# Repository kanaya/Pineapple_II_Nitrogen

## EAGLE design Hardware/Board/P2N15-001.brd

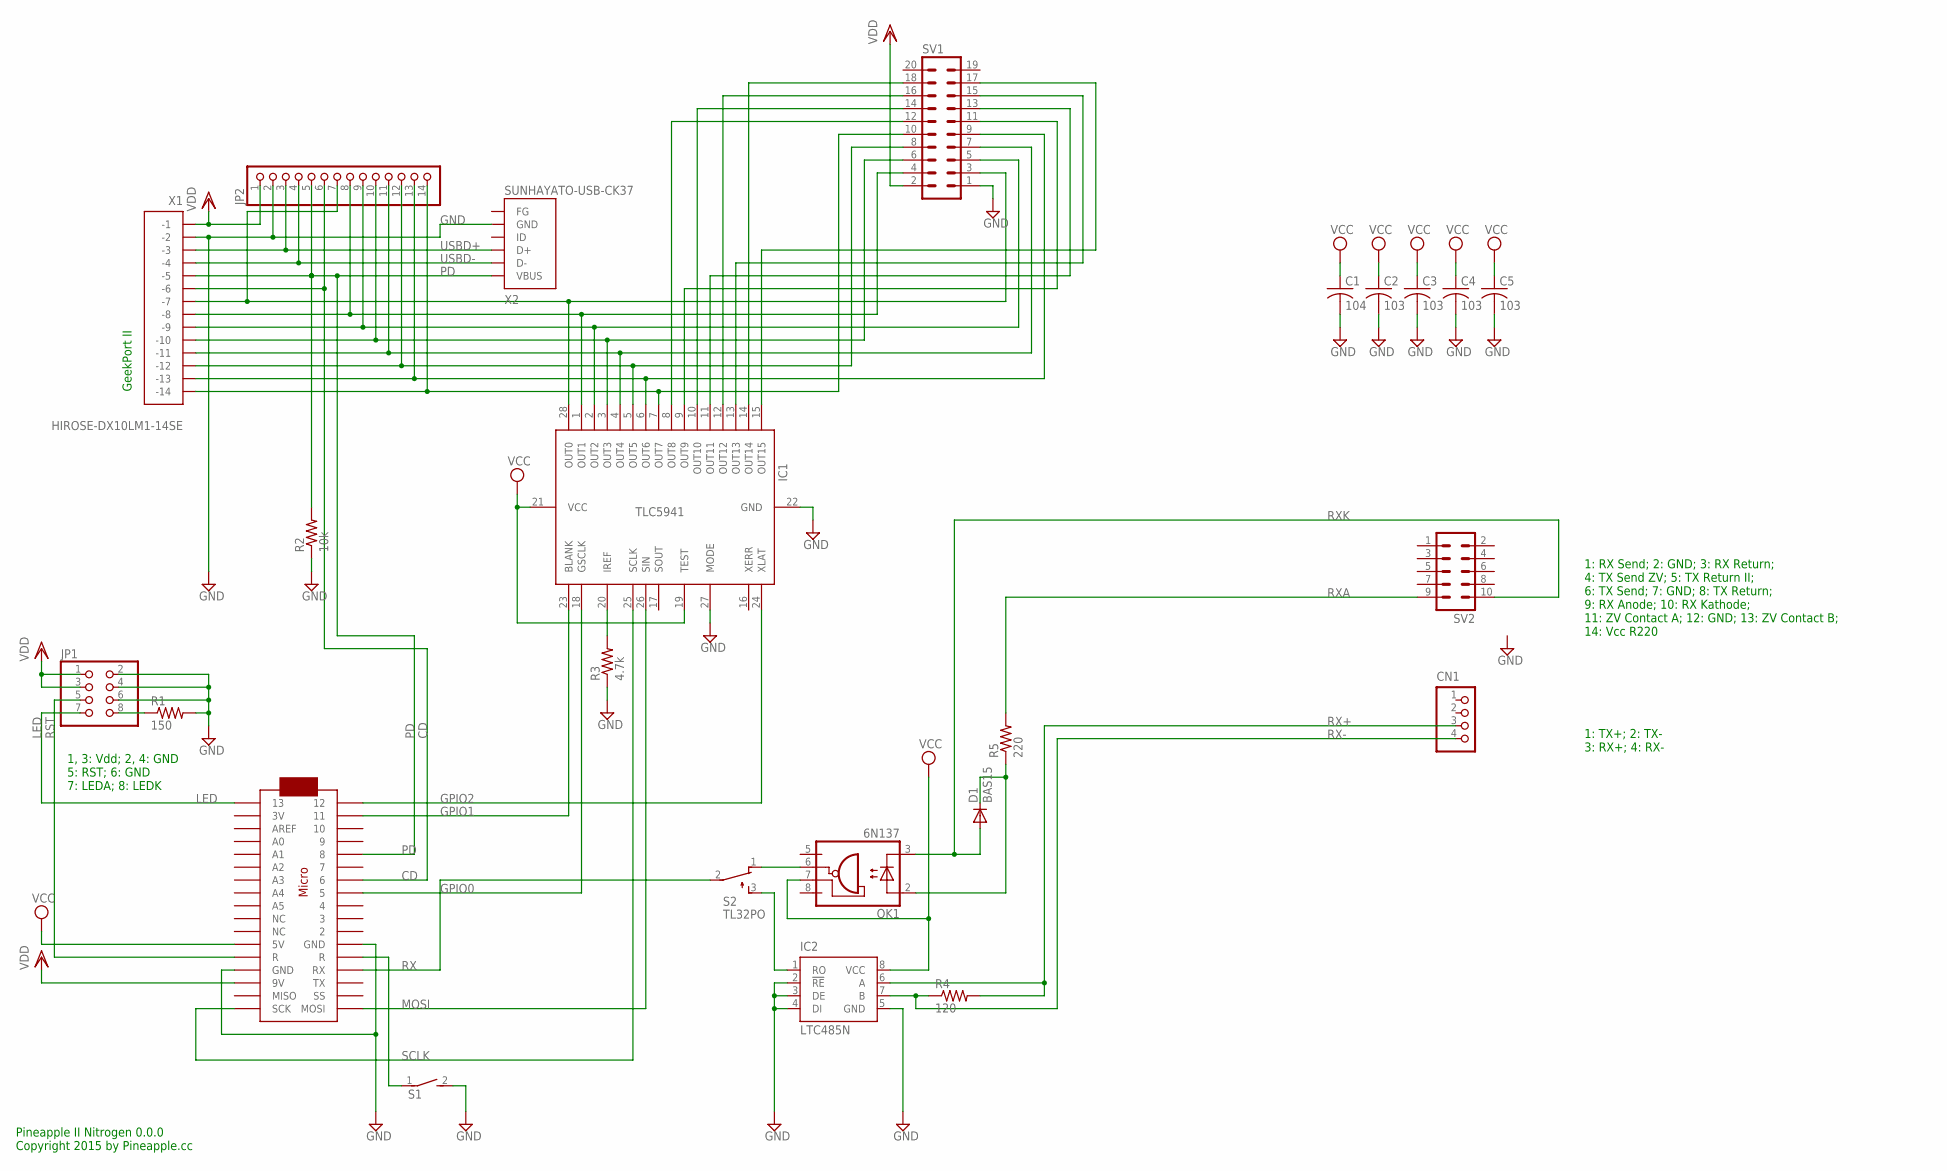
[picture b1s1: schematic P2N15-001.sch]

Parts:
C1: 104; C025-025X050
C2, C3, C4, C5: 103; C025-025X050
CN1: S4B-PH-K-S
D1: BAS15; DO34-7
IC1: TLC5941NT; DIL28-3
IC2: LTC485N; DIL08
JP1: PINHD-2X4; 2X04
JP2: PINHD-1X14-CB; 1X14-CB
MC1: ARDUINOMICRO
OK1: 6N137; DIL08
R1: 150; 0204/5
R2: 10k; 0204/5
R3: 4.7k; 0204/5
R4: 120; 0204/5
R5: 220; 0204/5
S1: DS01E; DS-01
S2: TL32PO; TL3XPO
SV1: ML20L
SV2: ML10L
X1: HIROSE-DX10LM1-14SE
X2: SUNHAYATO-USB-CK37

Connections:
CD: JP2.6, MC1.P$7 (6), X1.P$6 (-6)
GND: C1.2, C2.2, C3.2, C4.2, C5.2, IC1.22 (GND), IC1.27 (MODE), IC2.2 (!RE), IC2.3 (DE), IC2.4 (DI), IC2.5 (GND), JP1.2, JP1.4, JP1.6, JP2.2, MC1.P$12 (GND), MC1.P$21 (GND), R1.2, R2.1, R3.1, S1.2, SV1.1, X1.P$2 (-2), X2.P$5 (GND)
GPIO0: IC1.18 (GSCLK), MC1.P$8 (5)
GPIO1: IC1.23 (BLANK), MC1.P$2 (11)
GPIO2: IC1.24 (XLAT), MC1.P$1 (12)
LED: JP1.7, MC1.P$34 (13)
MIDIRX: OK1.6 (VO), S2.1 (O)
MOSI: IC1.26 (SIN), MC1.P$17 (MOSI)
unnamed: MC1.P$22 (R), S1.1
unnamed: IC2.1 (RO), S2.3 (S)
unnamed: IC1.28 (OUT0), JP2.7, SV1.3, X1.P$7 (-7)
unnamed: IC1.20 (IREF), R3.2
unnamed: IC1.7 (OUT7), JP2.14, SV1.10, X1.P$14 (-14)
unnamed: IC1.8 (OUT8), SV1.12
unnamed: IC1.1 (OUT1), JP2.8, SV1.4, X1.P$8 (-8)
unnamed: IC1.9 (OUT9), SV1.11
unnamed: IC1.2 (OUT2), JP2.9, SV1.5, X1.P$9 (-9)
unnamed: IC1.3 (OUT3), JP2.10, SV1.6, X1.P$10 (-10)
unnamed: IC1.4 (OUT4), JP2.11, SV1.7, X1.P$11 (-11)
unnamed: IC1.10 (OUT10), SV1.14
unnamed: IC1.11 (OUT11), SV1.13
unnamed: IC1.12 (OUT12), SV1.16
unnamed: D1.C, OK1.2 (A), R5.1
unnamed: IC1.13 (OUT13), SV1.15
unnamed: IC1.14 (OUT14), SV1.18
unnamed: IC1.15 (OUT15), SV1.17
unnamed: IC1.5 (OUT5), JP2.12, SV1.8, X1.P$12 (-12)
unnamed: IC1.6 (OUT6), JP2.13, SV1.9, X1.P$13 (-13)
unnamed: JP1.8, R1.1
PD: JP2.5, MC1.P$5 (8), R2.2, X1.P$5 (-5), X2.P$1 (VBUS)
RST: JP1.5, MC1.P$13 (R)
RX: MC1.P$14 (RX), S2.2
RX+: CN1.3, IC2.6 (A), R4.2
RX-: CN1.4, IC2.7 (B), R4.1
RXA: R5.2, SV2.9
RXK: D1.A, OK1.3 (C), SV2.10
SCLK: IC1.25 (SCLK), MC1.P$18 (SCK)
USBD+: JP2.3, X1.P$3 (-3), X2.P$3 (D+)
USBD-: JP2.4, X1.P$4 (-4), X2.P$2 (D-)
VCC: C1.1, C2.1, C3.1, C4.1, C5.1, IC1.19 (TEST), IC1.21 (VCC), IC2.8 (VCC), MC1.P$23 (5V), OK1.7 (VE)
VDD: JP1.1, JP1.3, JP2.1, MC1.P$20 (9V), SV1.2, X1.P$1 (-1)

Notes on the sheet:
Pineapple II Nitrogen 0.0.0 Copyright 2015 by Pineapple.cc
1, 3: Vdd; 2, 4: GND 5: RST; 6: GND 7: LEDA; 8: LEDK
GeekPort II
1: TX+; 2: TX- 3: RX+; 4: RX-
1: RX Send; 2: GND; 3: RX Return; 4: TX Send ZV; 5: TX Return II; 6: TX Send; 7: GND; 8: TX Return; 9: RX Anode; 10: RX Kathode; 11: ZV Contact A; 12: GND; 13: ZV Contact B; 14: Vcc R220

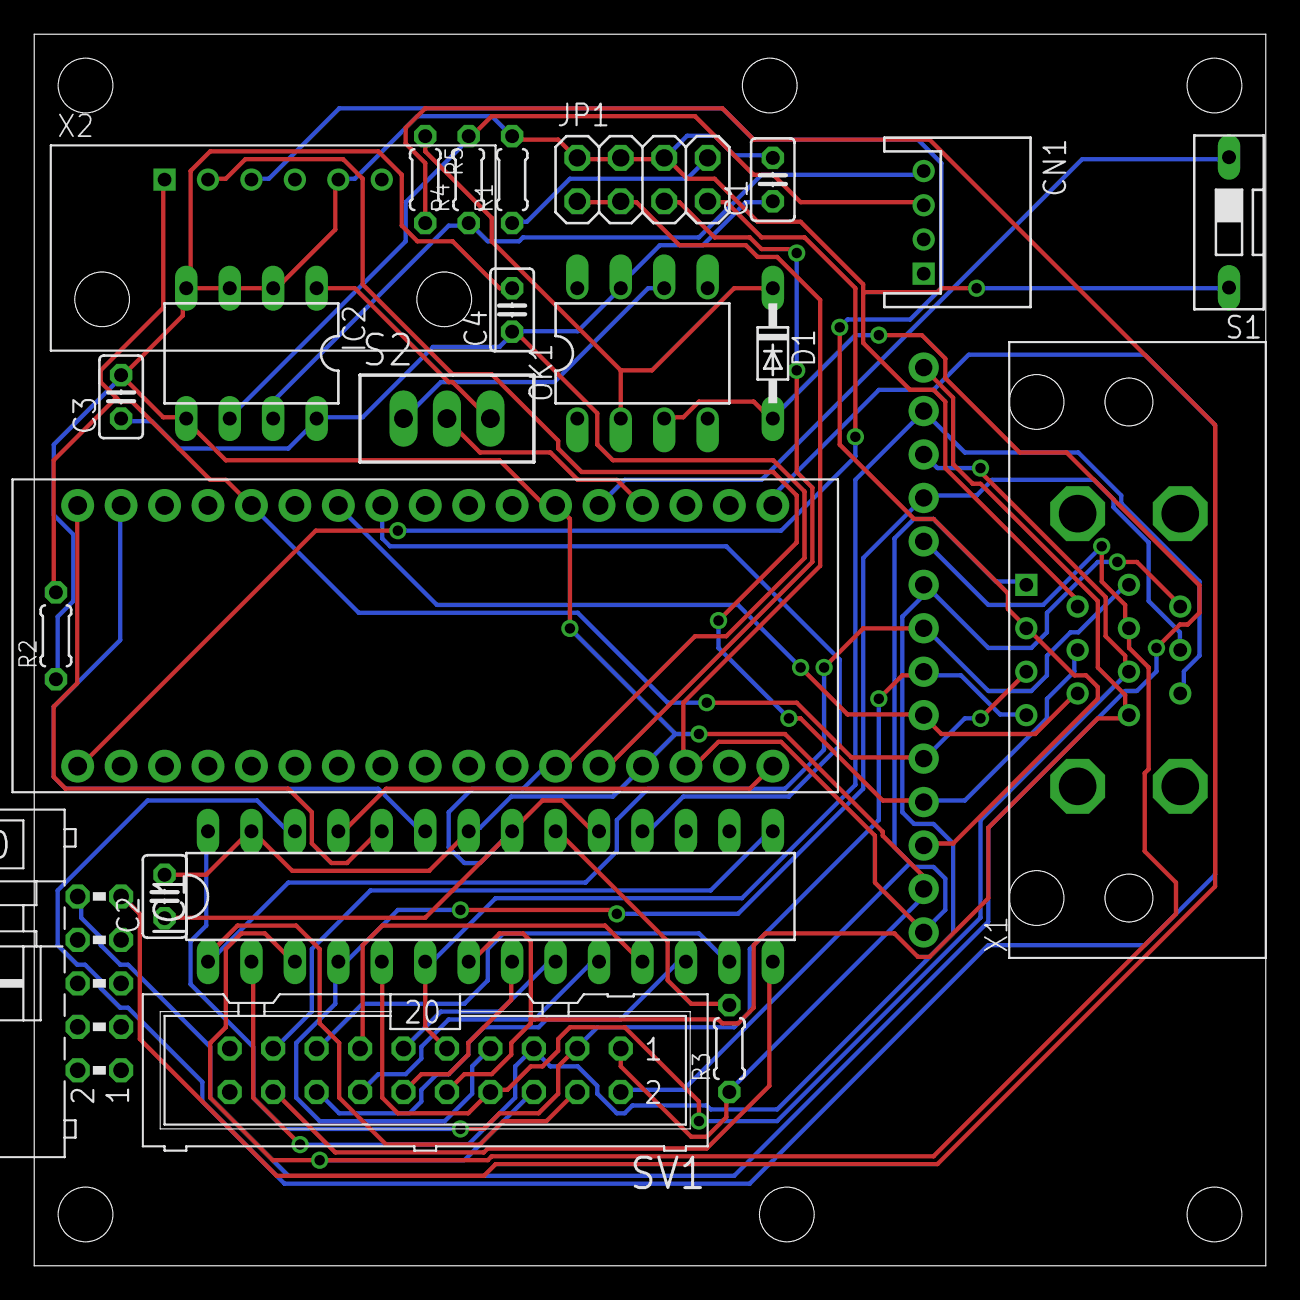
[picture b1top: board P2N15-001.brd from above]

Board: 2 copper layers, 72.0 x 72.0 mm, 23 parts (0 on the bottom side), 41 nets.

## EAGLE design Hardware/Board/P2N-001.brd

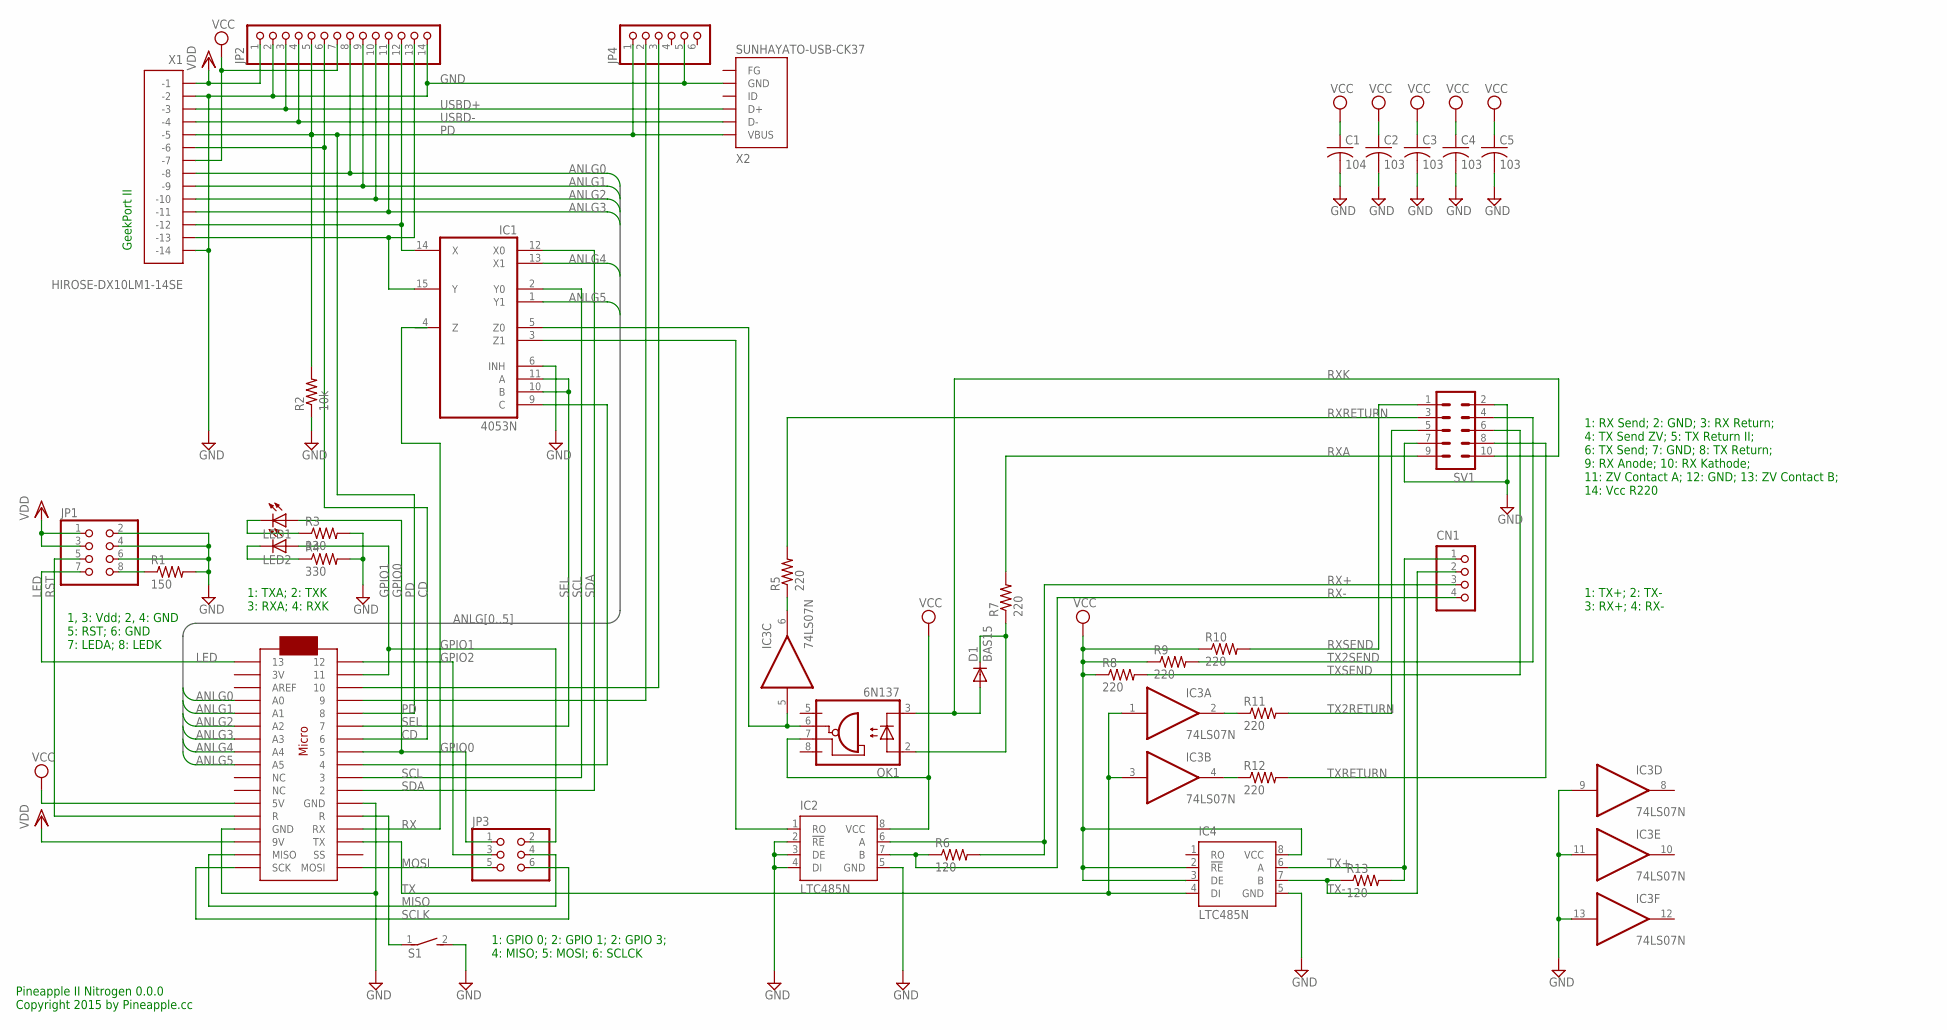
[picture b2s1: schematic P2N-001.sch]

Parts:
C1: 104; C025-025X050
C2, C3, C4, C5: 103; C025-025X050
CN1: S4B-PH-K-S
D1: BAS15; DO34-7
IC1: 4053N; DIL16
IC2, IC4: LTC485N; DIL08
IC3: 74LS07N; DIL14
JP1: PINHD-2X4; 2X04
JP2: PINHD-1X14-CB; 1X14-CB
JP3: PINHD-2X3; 2X03
JP4: PINHD-1X6; 1X06
LED1, LED2: LED3MM
MC1: ARDUINOMICRO
OK1: 6N137; DIL08
R1: 150; 0204/5
R2: 10k; 0204/5
R3, R4: 330; 0204/5
R5, R7, R8, R9, R10, R11, R12: 220; 0204/5
R6, R13: 120; 0204/5
S1: DS01E; DS-01
SV1: ML10L
X1: HIROSE-DX10LM1-14SE
X2: SUNHAYATO-USB-CK37

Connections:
ANLG0: JP2.8, MC1.P$31 (A0), X1.P$8 (-8)
ANLG1: JP2.9, MC1.P$30 (A1), X1.P$9 (-9)
ANLG2: JP2.10, MC1.P$29 (A2), X1.P$10 (-10)
ANLG3: JP2.11, MC1.P$28 (A3), X1.P$11 (-11)
ANLG4: IC1.13 (X1), MC1.P$27 (A4)
ANLG5: IC1.1 (Y1), MC1.P$26 (A5)
CD: JP2.6, MC1.P$7 (6), X1.P$6 (-6)
GND: C1.2, C2.2, C3.2, C4.2, C5.2, IC1.6 (INH), IC1.8 (GND), IC2.2 (!RE), IC2.3 (DE), IC2.4 (DI), IC2.5 (GND), IC3.7 (GND), IC3.9 (I), IC3.11 (I), IC3.13 (I), IC4.5 (GND), JP1.2, JP1.4, JP1.6, JP2.2, JP2.14, JP4.5, MC1.P$12 (GND), MC1.P$21 (GND), R1.2, R2.1, R3.2, R4.2, S1.2, SV1.2, SV1.7, X1.P$2 (-2), X1.P$14 (-14), X2.P$5 (GND)
GPIO0: JP3.1, LED1.A, MC1.P$8 (5)
GPIO1: JP3.2, LED2.A, MC1.P$2 (11)
GPIO2: JP3.3, MC1.P$1 (12)
LED: JP1.7, MC1.P$34 (13)
MIDIRX: IC1.5 (Z0), IC3.5 (I), OK1.6 (VO)
MISO: JP3.4, MC1.P$19 (MISO)
MOSI: JP3.5, MC1.P$17 (MOSI)
unnamed: MC1.P$22 (R), S1.1
unnamed: IC3.2 (O), R11.1
unnamed: IC3.6 (O), R5.1
unnamed: IC3.4 (O), R12.1
unnamed: JP4.2, MC1.P$4 (9)
unnamed: JP4.3, MC1.P$3 (10)
unnamed: IC1.9 (C), MC1.P$9 (4)
unnamed: D1.C, OK1.2 (A), R7.1
unnamed: LED1.K (C), R3.1
unnamed: LED2.K (C), R4.1
unnamed: IC1.14 (X), JP2.12, X1.P$12 (-12)
unnamed: IC1.15 (Y), JP2.13, X1.P$13 (-13)
unnamed: JP1.8, R1.1
PD: JP2.5, JP4.1, MC1.P$5 (8), R2.2, X1.P$5 (-5), X2.P$1 (VBUS)
RST: JP1.5, MC1.P$13 (R)
RX: MC1.P$14 (RX)
RX+: CN1.3, IC2.6 (A), R6.2
RX-: CN1.4, IC2.7 (B), R6.1
RXA: R7.2, SV1.9
RXK: D1.A, OK1.3 (C), SV1.10
RXRETURN: R5.2, SV1.3
RXSEND: R10.2, SV1.1
SCL: IC1.2 (Y0), MC1.P$10 (3)
SCLK: JP3.6, MC1.P$18 (SCK)
SDA: IC1.12 (X0), MC1.P$11 (2)
SEL: IC1.10 (B), IC1.11 (A), MC1.P$6 (7)
TX: IC3.1 (I), IC3.3 (I), IC4.4 (DI), MC1.P$15 (TX)
TX2RETURN: R11.2, SV1.5
TX2SEND: R9.2, SV1.4
TX+: CN1.1, IC4.6 (A), R13.2
TX-: CN1.2, IC4.7 (B), R13.1
TXRETURN: R12.2, SV1.8
TXSEND: R8.2, SV1.6
USBD+: JP2.3, X1.P$3 (-3), X2.P$3 (D+)
USBD-: JP2.4, X1.P$4 (-4), X2.P$2 (D-)
VCC: C1.1, C2.1, C3.1, C4.1, C5.1, IC1.16 (VCC), IC2.8 (VCC), IC3.14 (VCC), IC4.2 (!RE), IC4.3 (DE), IC4.8 (VCC), JP2.7, MC1.P$23 (5V), OK1.7 (VE), R8.1, R9.1, R10.1, X1.P$7 (-7)
VDD: JP1.1, JP1.3, JP2.1, MC1.P$20 (9V), X1.P$1 (-1)
VEE: IC1.7 (VEE)
XMIDIRX: IC1.3 (Z1), IC2.1 (RO)

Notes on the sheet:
Pineapple II Nitrogen 0.0.0 Copyright 2015 by Pineapple.cc
1, 3: Vdd; 2, 4: GND 5: RST; 6: GND 7: LEDA; 8: LEDK
GeekPort II
1: TXA; 2: TXK 3: RXA; 4: RXK
1: TX+; 2: TX- 3: RX+; 4: RX-
1: GPIO 0; 2: GPIO 1; 2: GPIO 3; 4: MISO; 5: MOSI; 6: SCLCK
1: RX Send; 2: GND; 3: RX Return; 4: TX Send ZV; 5: TX Return II; 6: TX Send; 7: GND; 8: TX Return; 9: RX Anode; 10: RX Kathode; 11: ZV Contact A; 12: GND; 13: ZV Contact B; 14: Vcc R220

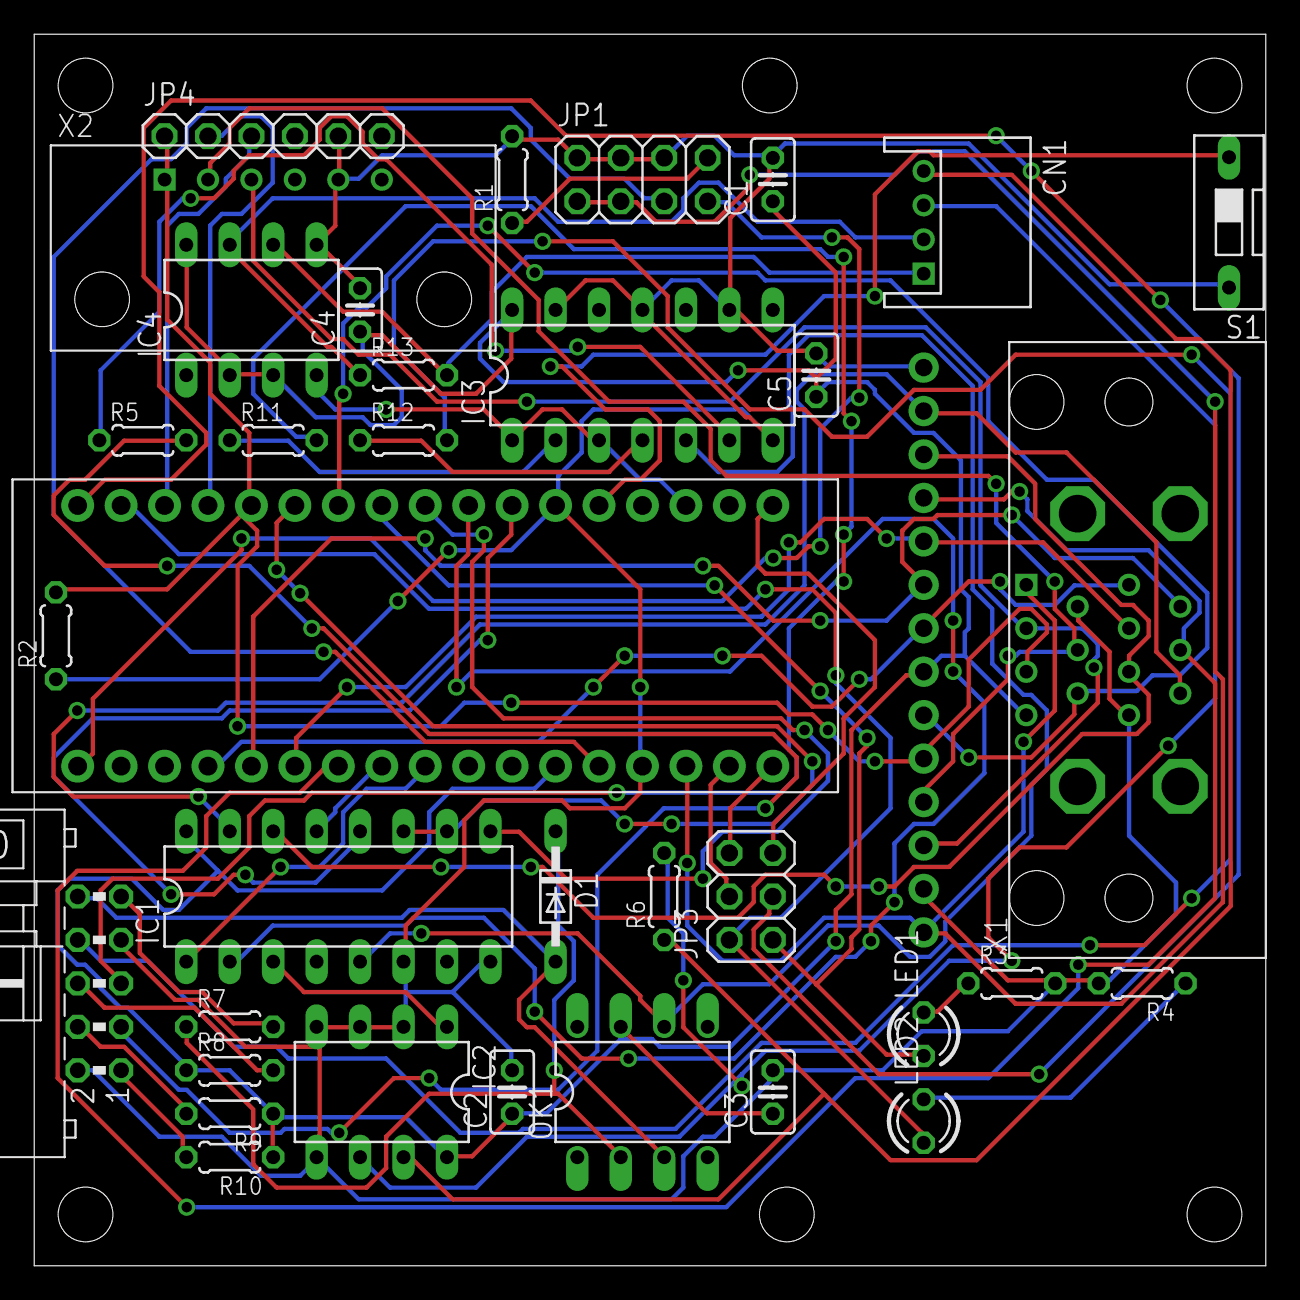
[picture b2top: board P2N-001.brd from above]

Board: 2 copper layers, 72.0 x 72.0 mm, 36 parts (0 on the bottom side), 52 nets.

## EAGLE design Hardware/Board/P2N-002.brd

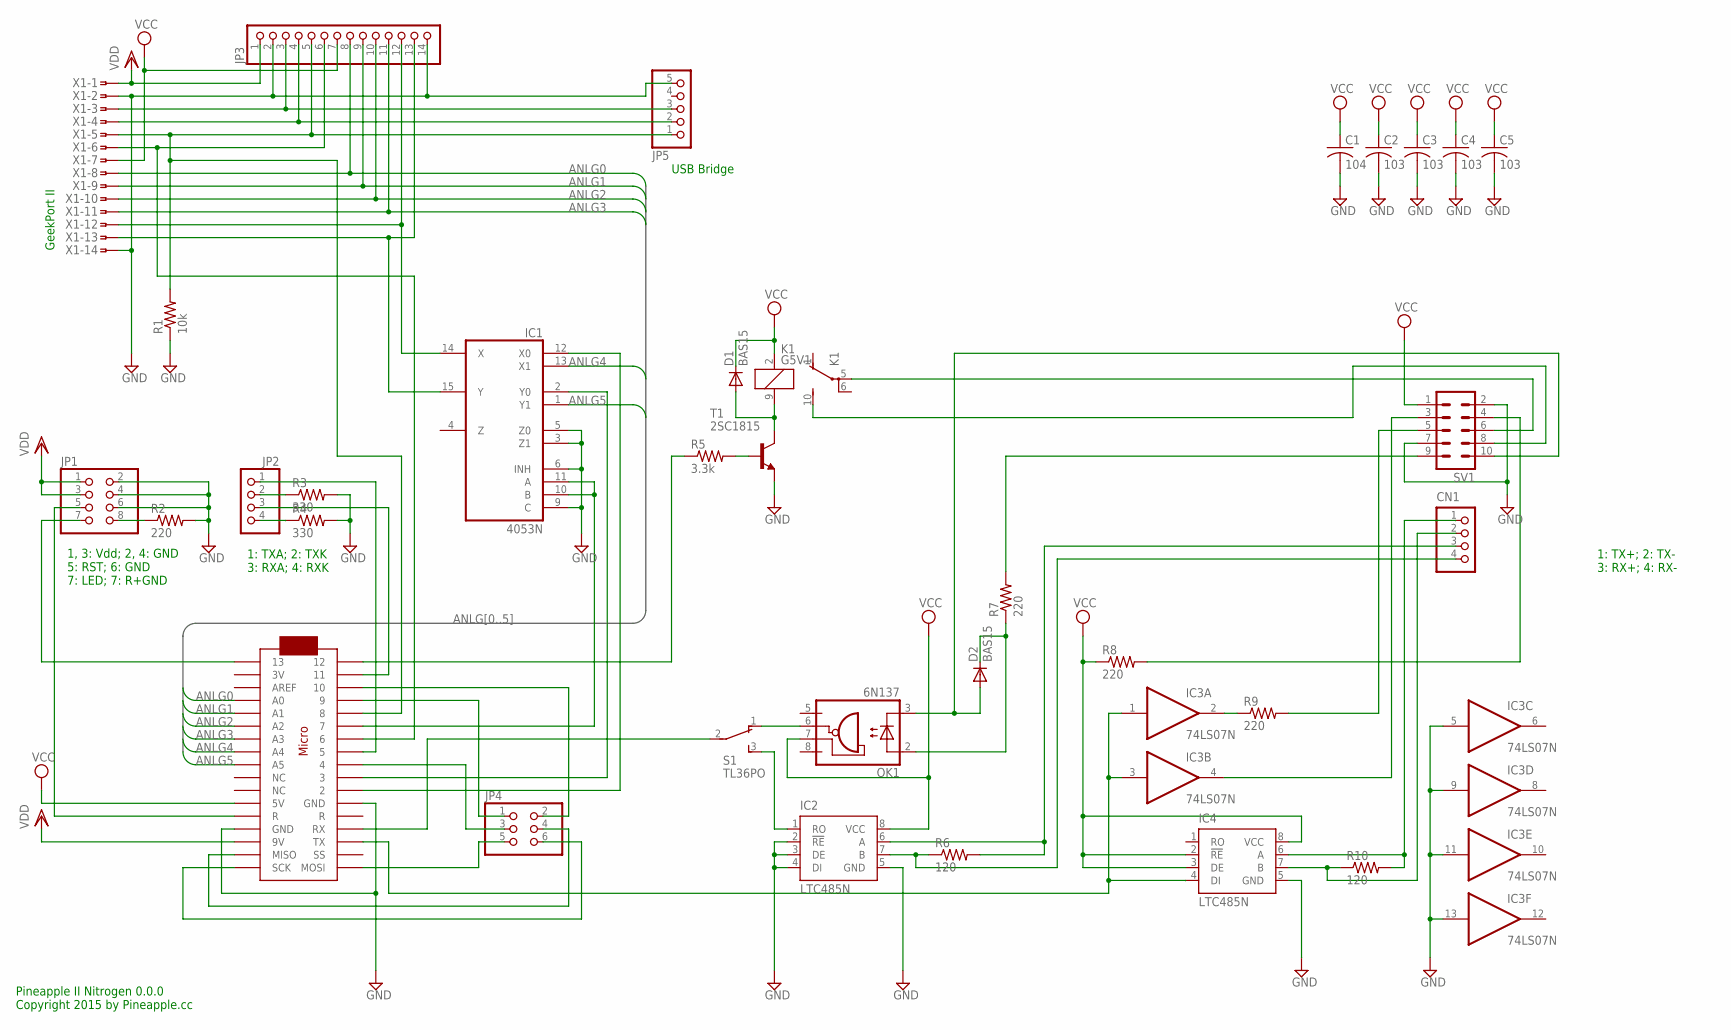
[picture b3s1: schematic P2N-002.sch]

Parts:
C1: 104; C025-025X050
C2, C3, C4, C5: 103; C025-025X050
CN1: S4B-PH-K-S
D1, D2: BAS15; DO34-7
IC1: 4053N; DIL16
IC2, IC4: LTC485N; DIL08
IC3: 74LS07N; DIL14
JP1: PINHD-2X4; 2X04
JP2: PINHD-1X4; 1X04
JP3: PINHD-1X14; 1X14
JP4: PINHD-2X3; 2X03
JP5: PINHD-1X5/90; 1X05/90
K1: G5V1
MC1: ARDUINOMICRO
OK1: 6N137; DIL08
R1: 10k; 0204/5
R2, R7, R8, R9: 220; 0204/5
R3, R4: 330; 0204/5
R5: 3.3k; 0204/5
R6, R10: 120; 0204/5
S1: TL36PO; TL3XPO
SV1: ML10L
T1: 2SC1815; TO92-ECB
X1: HIROSE-DXLM

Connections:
ANLG0: JP3.8, MC1.P$31 (A0), X1.8
ANLG1: JP3.9, MC1.P$30 (A1), X1.9
ANLG2: JP3.10, MC1.P$29 (A2), X1.10
ANLG3: JP3.11, MC1.P$28 (A3), X1.11
ANLG4: IC1.13 (X1), MC1.P$27 (A4)
ANLG5: IC1.1 (Y1), MC1.P$26 (A5)
GEEK16: IC1.10 (B), IC1.11 (A), MC1.P$6 (7)
GND: C1.2, C2.2, C3.2, C4.2, C5.2, IC1.3 (Z1), IC1.5 (Z0), IC1.6 (INH), IC1.8 (GND), IC1.9 (C), IC2.2 (!RE), IC2.3 (DE), IC2.4 (DI), IC2.5 (GND), IC3.5 (I), IC3.7 (GND), IC3.9 (I), IC3.11 (I), IC3.13 (I), IC4.5 (GND), JP1.2, JP1.4, JP1.6, JP3.2, JP3.14, JP5.5, MC1.P$12 (GND), MC1.P$21 (GND), R1.1, R2.2, R3.2, R4.2, SV1.2, SV1.7, T1.E, X1.2, X1.14
MIDI1: CN1.1, IC4.6 (A), R10.2
MIDI3: CN1.2, IC4.7 (B), R10.1
MIDI6: IC3.1 (I), IC3.3 (I), IC4.4 (DI), MC1.P$15 (TX)
MIDI11: CN1.3, IC2.6 (A), R6.2
MIDI13: CN1.4, IC2.7 (B), R6.1
MIDI15: D2.A, OK1.3 (C), SV1.10
MIDIRX: OK1.6 (VO), S1.1 (O)
unnamed: IC3.4 (O), SV1.3
unnamed: IC3.2 (O), R9.1
unnamed: JP1.5, MC1.P$13 (R)
unnamed: JP1.7, MC1.P$34 (13)
unnamed: R7.2, SV1.9
unnamed: D1.A, K1.9 (2), T1.C
unnamed: MC1.P$14 (RX), S1.2
unnamed: R5.2, T1.B
unnamed: JP4.3, MC1.P$9 (4)
unnamed: R9.2, SV1.5
unnamed: JP4.5, MC1.P$17 (MOSI)
unnamed: R8.2, SV1.4
unnamed: JP4.6, MC1.P$18 (SCK)
unnamed: K1.10 (S), SV1.8
unnamed: D2.C, OK1.2 (A), R7.1
unnamed: K1.5, SV1.6
unnamed: JP2.2, R3.1
unnamed: JP2.4, R4.1
unnamed: IC1.2 (Y0), MC1.P$10 (3)
unnamed: JP2.1, MC1.P$8 (5)
unnamed: JP2.3, MC1.P$2 (11)
unnamed: MC1.P$1 (12), R5.1
unnamed: IC1.12 (X0), MC1.P$11 (2)
unnamed: JP3.5, JP5.1, MC1.P$5 (8), R1.2, X1.5
unnamed: JP3.4, JP5.2, X1.4
unnamed: JP3.3, JP5.3, X1.3
unnamed: JP3.6, MC1.P$7 (6), X1.6
unnamed: IC1.14 (X), JP3.12, X1.12
unnamed: IC1.15 (Y), JP3.13, X1.13
unnamed: JP4.1, MC1.P$4 (9)
unnamed: JP4.2, MC1.P$3 (10)
unnamed: JP1.8, R2.1
unnamed: JP4.4, MC1.P$19 (MISO)
VCC: C1.1, C2.1, C3.1, C4.1, C5.1, D1.C, IC1.16 (VCC), IC2.8 (VCC), IC3.14 (VCC), IC4.2 (!RE), IC4.3 (DE), IC4.8 (VCC), JP3.7, K1.2 (1), MC1.P$23 (5V), OK1.7 (VE), R8.1, SV1.1, X1.7
VDD: JP1.1, JP1.3, JP3.1, MC1.P$20 (9V), X1.1
VEE: IC1.7 (VEE)
XMIDIRX: IC2.1 (RO), S1.3 (S)

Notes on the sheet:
Pineapple II Nitrogen 0.0.0 Copyright 2015 by Pineapple.cc
1, 3: Vdd; 2, 4: GND 5: RST; 6: GND 7: LED; 7: R+GND
GeekPort II
USB Bridge
1: TXA; 2: TXK 3: RXA; 4: RXK
1: TX+; 2: TX- 3: RX+; 4: RX-

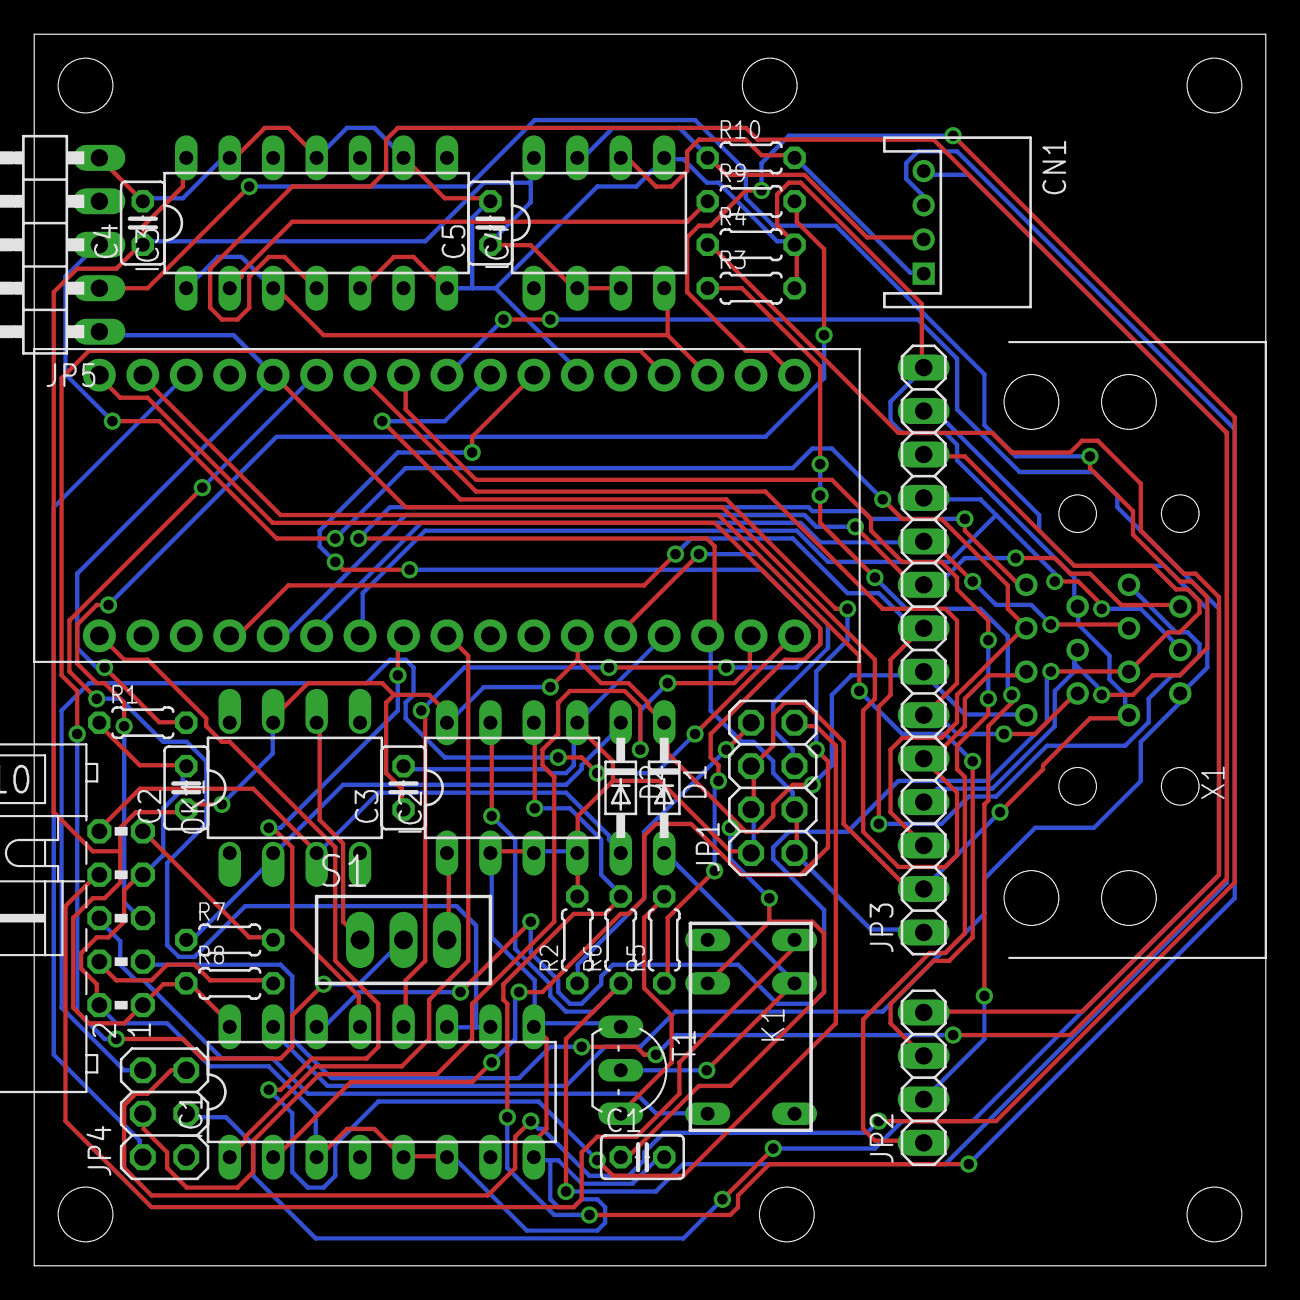
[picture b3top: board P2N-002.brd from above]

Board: 2 copper layers, 72.0 x 72.0 mm, 34 parts (0 on the bottom side), 51 nets.

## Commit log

2015-04-05 Added Documents.
2015-04-05 Added Hardware/Board.
2015-04-05 Added Panels.
2015-04-07 Cleaned up panel layouts and made order sheet for Takachi.
2015-04-07 Removed Takachis template order sheet.
2015-04-08 Some pinouts were replaced.
2015-04-08 New board design.
2015-04-08 PH straight -> PH bended.
2015-04-08 Rerouted the board.
2015-04-09 Added silk patterns.
2015-04-13 Fixed something.
2015-04-13 New circuit design. (Experimental.)
2015-04-13 Changed XMIDI layout.
2015-04-13 New pinout.
2015-04-13 Doc for new pinout.
2015-04-13 Canceled change of XMIDI layout.
2015-04-13 New layout.
2015-04-14 Changed MIDI IN/OUT layout.
2015-04-14 Internal drive port.
2015-04-14 Rerouted.
2015-04-14 Removed P2N-001.{brd,sch}.
2015-04-14 Renamed P2N-002.{brd,sch} to P2N-001.{brd,sch}.
2015-04-14 Update document.
2015-04-14 Renamed pinout.
2015-04-14 Added comment.
2015-04-14 Modified pinout.
2015-04-14 Added pinout of "Pro Micro" version.
2015-04-14 Added "ports" doc.
2015-04-14 Labeled wires.
2015-04-14 Minor fixes.
2015-04-15 Added anther LED pattern.
2015-04-15 Fixed error of doc.
2015-04-15 No change.
2015-04-15 Removed unnecessary layer from panel layout.
2015-04-15 Added logicboard layer to panel1.ai.
2015-04-15 Removed LED jumper.
2015-04-15 Cleaned up panel layout.
2015-04-16 Added panel-layout PDF.
2015-04-16 Added N15.
2015-04-16 Attached LED pattern to GPIO pins.
2015-04-16 Cleaned up schematic and board design of P2N.
2015-04-16 Added pinouts of N15.
2015-04-17 Added LED monitors to P2N15.
2015-04-17 Added Reset SW.
2015-04-17 Added notes of N15.
2015-04-17 Added MIDI THRU function.
2015-04-18 Updated Hirose DX10LM1-14SE connector pattern.
2015-04-21 Changed R value of main LED (from 220 to 150 ohm).
2015-04-21 Added PDF version of sch and brd of P2N-001 and P2N15-001.
2015-04-22 Changed 10p-backport to 14p-backport.
2015-04-22 Document update.
2015-04-22 Updated ports.md.
2015-04-22 Changed MIDI+ to XMIDI.
2015-04-22 Adopted to XMIDI.
2015-04-22 Cleaned up pinout doc.
2015-04-22 Cleaned up board design.
2015-04-22 Clean up of Doc.
2015-04-23 Changed USB connector from Pinheader to Micro-B.
2015-04-23 Changed USB con to Sunhayatos connector board. Changed USB connector to Sunhayato's connector board. Also removed ZeroVoltage function.
2015-04-24 Re-adjusted back panel for Hoshidens MIDI receptacle.
2015-04-24 Adjusted silk pattern of back panel.
2015-04-24 Changed logo of front panel to Pineapple II N.
2015-04-25 Clean up of docs.
2015-04-25 Reset of P2N15-001.{brd,sch}.
2015-04-25 Redesigned N15 board.
2015-04-26 Changed 20-p MIL connector type from right-angled to straight.
